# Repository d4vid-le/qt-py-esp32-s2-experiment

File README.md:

# qt-py-esp32-s2-experiment

A personal, non-production experiment: reconstruct the **Adafruit QT Py ESP32-S2
(Product 5325, Rev C)** in KiCad from the authoritative Eagle source, measuring
how accurately an AI agent can do it — and documenting every failure.

**This is not affiliated with or endorsed by Adafruit.** No boards are fabricated.

## Status

| Gate | Stage | Result |
|---|---|---|
| 0 | Inventory | ✅ 45 components, 34 nets, 159 pads; `.sch` vs `.brd` exact |
| 1 | Ground truth in KiCad | ✅ board imported; netlist identical after 2 ref renames; 57/57 pin audit |
| 2 | Schematic reconstruction | ✅ 45 components, 46 power symbols, 34/34 nets, 0 ERC errors |
| 3 | PCB | ✅ 45/45 placed, 17.78×20.701 outline, DRC run |
| 4 | Routing | ✅ 0 unconnected / 0 errors / 1.093 mm skew (verified reconstruction) |
| 5 | Manufacturing | ✅ Gerbers, drill, BOM, PnP, DFM, renders |

Read `reports/gate0-inventory.md`, `reports/gate1-ground-truth.md`,
`reports/gate1-u15-audit.md`, and `reports/gate2-schematic.md`.

## Attribution

The reference design is Adafruit's work, licensed **CC BY-SA 3.0 Unported**.
Verified in the source repository's
[`license.txt`](https://github.com/adafruit/Adafruit-QT-Py-ESP32-S2-PCB/blob/main/license.txt)
(shasum `075dad5e…86b74`):

- Product: https://www.adafruit.com/product/5325
- Learn guide: https://learn.adafruit.com/adafruit-qt-py-esp32-s2
- Downloads: https://learn.adafruit.com/adafruit-qt-py-esp32-s2/downloads
- Authoritative Eagle source: https://github.com/adafruit/Adafruit-QT-Py-ESP32-S2-PCB
- ESP32-S2 datasheet: https://cdn-learn.adafruit.com/assets/assets/000/096/705/original/esp32-s2_datasheet_en.pdf
- AP2112 datasheet: https://www.diodes.com/assets/Datasheets/AP2112.pdf

**Their Eagle files, PDFs and images are not committed here.** `reference/` is
gitignored; run `scripts/fetch-reference.sh` to pull them locally.

## Reproduce the netlist

```sh
scripts/fetch-reference.sh
python3 scripts/parse_eagle_netlist.py \
  "reference/eagle/Adafruit QT Py ESP32-S2 Rev C.sch" design
python3 scripts/compare_sch_brd.py \
  design/netlist_original.csv \
  "reference/eagle/Adafruit QT Py ESP32-S2 Rev C.brd"
python3 scripts/make_clean_bom.py \
  design/bom_original.csv design/bom_clean.csv design/bom_symbols.csv
```

Pin audit (needs PyMuPDF: `pip install -r scripts/requirements.txt`):

```sh
python3 scripts/parse_esp32s2_pins.py \
  reference/assets/esp32-s2_datasheet.pdf reference/imported-kicad/esp32s2-pins.csv
python3 scripts/make_u15_audit.py \
  "reference/eagle/Adafruit QT Py ESP32-S2 Rev C.sch" \
  reference/imported-kicad/esp32s2-pins.csv \
  design/netlist_original.csv design/u15-pinmap.csv
```

Import the board and diff it:

```sh
kicad-cli pcb import --format eagle \
  -o reference/imported-kicad/qt-py-esp32-s2.kicad_pcb \
  "reference/eagle/Adafruit QT Py ESP32-S2 Rev C.brd"

python3 scripts/extract_kicad_netlist.py \
  reference/imported-kicad/qt-py-esp32-s2.kicad_pcb \
  reference/imported-kicad/imported_netlist.csv

python3 scripts/diff_netlists.py \
  design/netlist_original.csv \
  reference/imported-kicad/imported_netlist.csv
```

## Layout

```
design/     ground-truth CSVs, STATE.md, checksums   (committed)
reports/    per-gate evidence                        (committed)
scripts/    parser, diff, fetch                      (committed)
renders/    PNG/JPG evidence                         (committed)
rebuild/    the KiCad reconstruction                 (Gate 2+)
reference/  Adafruit material + imported board       (gitignored)
```

## What is deliberately not here

- Adafruit's Eagle/PDF/image files (license + redistribution hygiene)
- `reference/`, venvs, `node_modules/`, secrets, logs
- Fabrication files: nothing is ordered or produced for manufacturing

## Notes

- KiCad 10.0.7, macOS arm64.
- The Eagle importer maps custom user layers 200/201 to `UNDEFINED`, which makes
  the imported board unloadable by DRC. Electrical data is unaffected. See the
  Gate 1 report.
- `kicad-sch-api` is not used: it does not embed `lib_symbols`.

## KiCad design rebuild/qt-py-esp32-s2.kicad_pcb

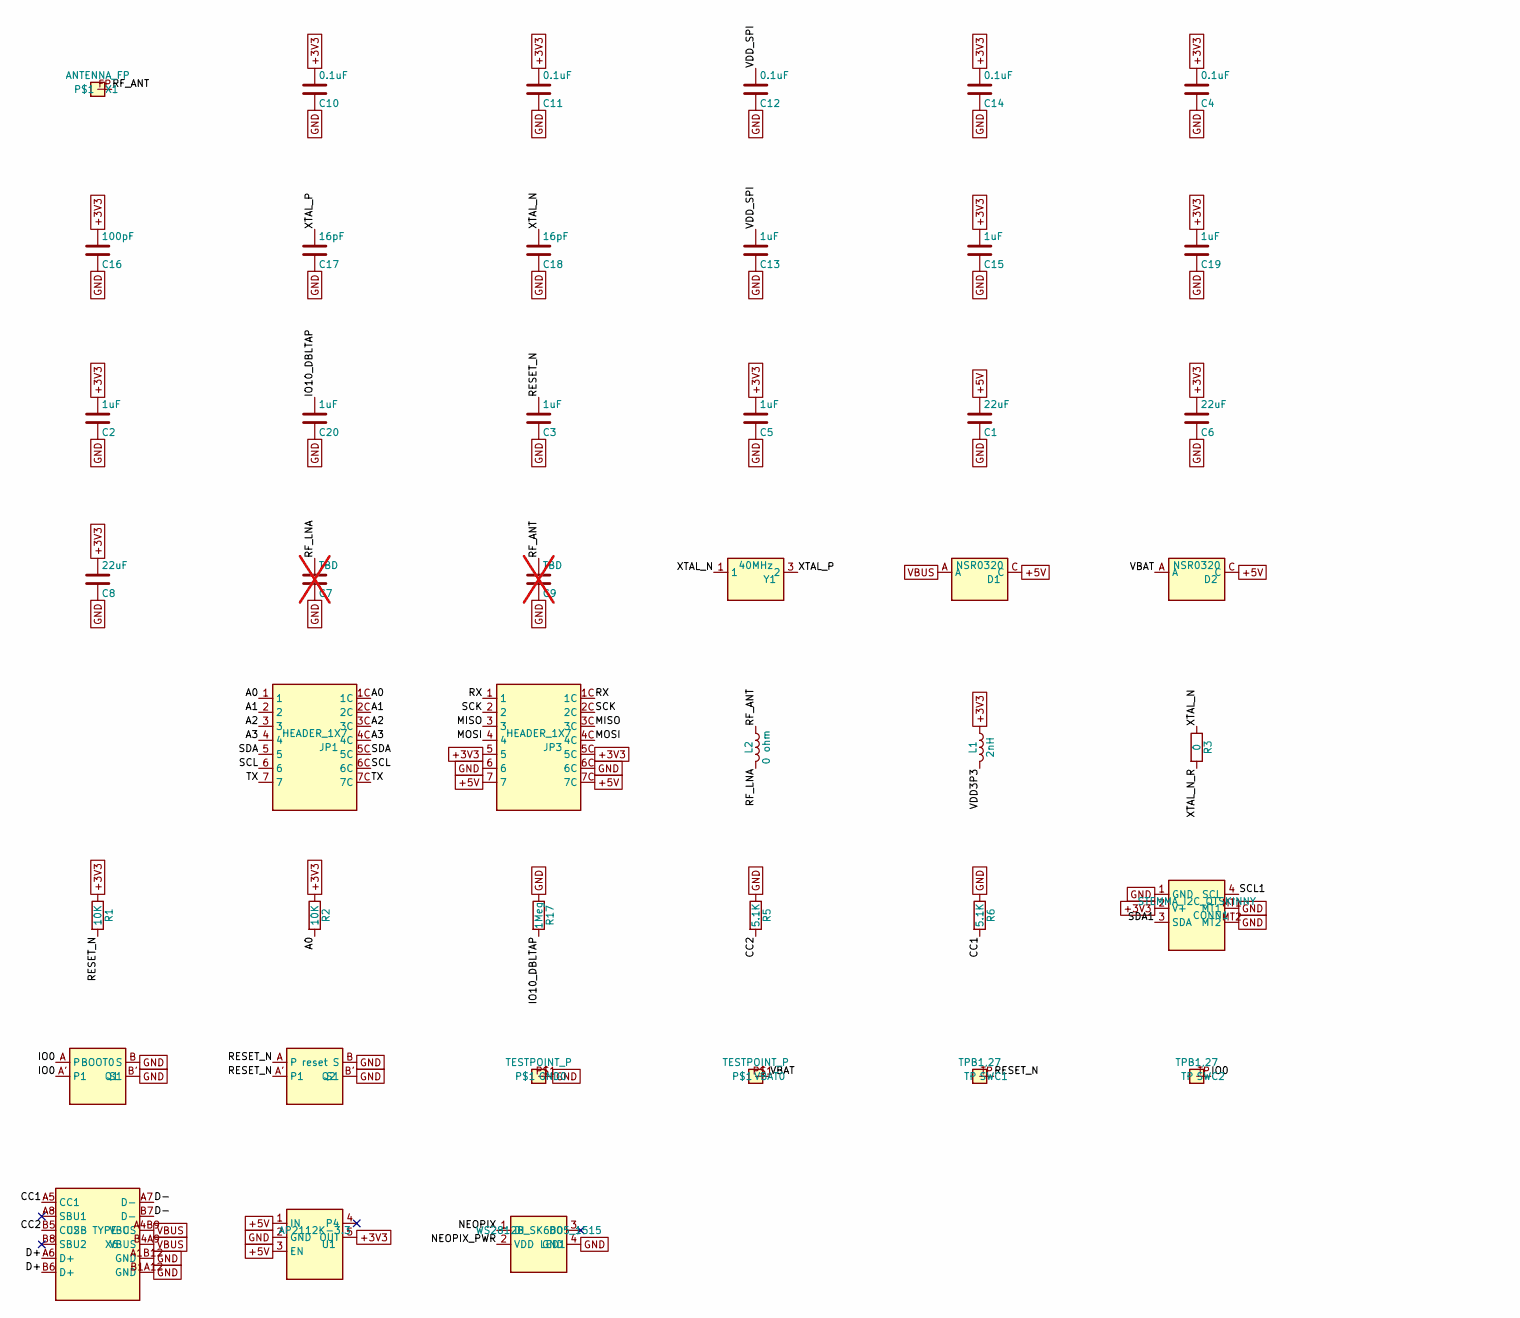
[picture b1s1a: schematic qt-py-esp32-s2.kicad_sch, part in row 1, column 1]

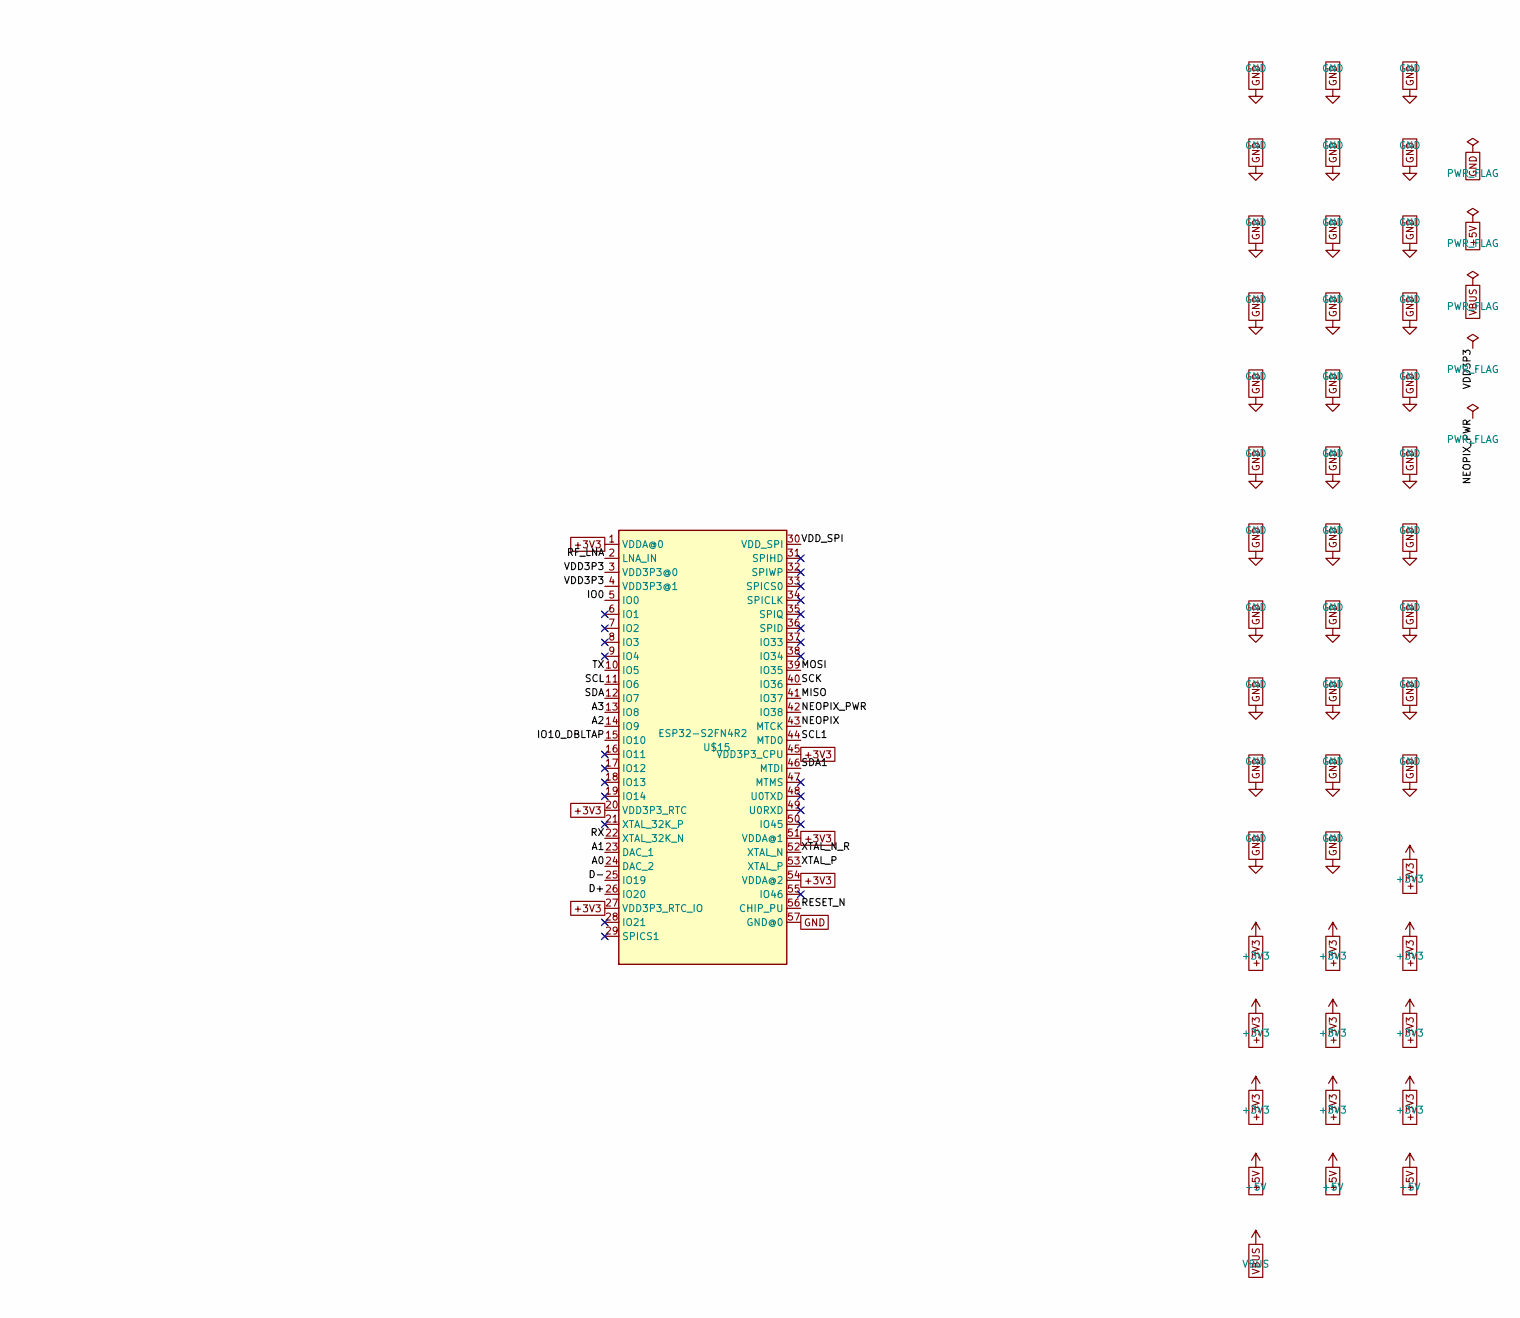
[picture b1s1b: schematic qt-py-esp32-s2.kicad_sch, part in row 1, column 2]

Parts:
C1, C6, C8: 22uF; C_0805_2012Metric
C2, C3, C5, C13, C15, C19, C20: 1uF; C_0402_1005Metric
C4, C10, C11, C12, C14: 0.1uF; C_0402_1005Metric
C7, C9: TBD; C_0402_1005Metric; not fitted
C16: 100pF; C_0402_1005Metric
C17, C18: 16pF; C_0402_1005Metric
CONN1: STEMMA_I2C_QTSKINNY; JST_SH4_SKINNY
D1, D2: NSR0320; SOD-323_MINI
GND0: TESTPOINT_P; TESTPOINT_MINUS_1X3MM
JP1, JP3: HEADER_1X7; 1X07_CASTEL
L1: 2nH; L_0402_1005Metric
L2: 0 ohm; L_0402_1005Metric
LED1: WS2812B_SK6805_1515; SK6805_1515
Q1: BOOT0; BTN_KMR2_4.6X2.8
Q2: reset; BTN_KMR2_4.6X2.8
R1, R2: 10K; R_0402_1005Metric
R3: 0; R_0402_1005Metric
R5, R6: 5.1K; R_0402_1005Metric
R17: 1Meg; R_0402_1005Metric
SWC1, SWC2: TPB1,27; B1_27
U1: AP2112K-3.3; SOT23-5
U$15: ESP32-S2FN4R2; QFN56_7X7
VBAT0: TESTPOINT_P; TESTPOINT_PLUS_1X3MM
X1: ANTENNA_FP; ANT_2450AT18B100
X6: USB TYPE C; USB_C_CUSB31-CFM2AX-01-X
Y1: 40MHz; CRYSTAL_2X1.6

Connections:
+3V3: C2.1, C4.1, C5.1, C6.1, C8.1, C10.1, C11.1, C14.1, C15.1, C16.1, C19.1, CONN1.2 (V+), JP3.5, JP3.5C, L1.1, R1.1, R2.1, U1.5 (OUT), U$15.1 (VDDA@0), U$15.20 (VDD3P3_RTC), U$15.27 (VDD3P3_RTC_IO), U$15.45 (VDD3P3_CPU), U$15.51 (VDDA@1), U$15.54 (VDDA@2)
+5V: C1.1, D1.C, D2.C, JP3.7, JP3.7C, U1.1 (IN), U1.3 (EN)
A0: JP1.1, JP1.1C, R2.2, U$15.24 (DAC_2)
A1: JP1.2, JP1.2C, U$15.23 (DAC_1)
A2: JP1.3, JP1.3C, U$15.14 (IO9)
A3: JP1.4, JP1.4C, U$15.13 (IO8)
CC1: R6.2, X6.A5 (CC1)
CC2: R5.2, X6.B5 (CC2)
D+: U$15.26 (IO20), X6.A6 (D+), X6.B6 (D+)
D-: U$15.25 (IO19), X6.A7 (D-), X6.B7 (D-)
GND: C1.2, C2.2, C3.2, C4.2, C5.2, C6.2, C7.2, C8.2, C9.2, C10.2, C11.2, C12.2, C13.2, C14.2, C15.2, C16.2, C17.2, C18.2, C19.2, C20.2, CONN1.1 (GND), CONN1.MT1, CONN1.MT2, GND0.P$1, JP3.6, JP3.6C, LED1.4 (GND), Q1.B (S), Q1.B' (S1), Q2.B (S), Q2.B' (S1), R5.1, R6.1, R17.1, U1.2 (GND), U$15.57 (GND@0), X6.A1B12 (GND), X6.B1A12 (GND)
IO0: Q1.A, Q1.A' (P1), SWC2.TP, U$15.5 (IO0)
IO10_DBLTAP: C20.1, R17.2, U$15.15 (IO10)
MISO: JP3.3, JP3.3C, U$15.41 (IO37)
MOSI: JP3.4, JP3.4C, U$15.39 (IO35)
NEOPIX: LED1.1 (DI), U$15.43 (MTCK)
NEOPIX_PWR: LED1.2 (VDD), U$15.42 (IO38)
RESET_N: C3.1, Q2.A, Q2.A' (P1), R1.2, SWC1.TP, U$15.56 (CHIP_PU)
RF_ANT: C9.1, L2.1, X1.FP
RF_LNA: C7.1, L2.2, U$15.2 (LNA_IN)
RX: JP3.1, JP3.1C, U$15.22 (XTAL_32K_N)
SCK: JP3.2, JP3.2C, U$15.40 (IO36)
SCL: JP1.6, JP1.6C, U$15.11 (IO6)
SCL1: CONN1.4 (SCL), U$15.44 (MTD0)
SDA: JP1.5, JP1.5C, U$15.12 (IO7)
SDA1: CONN1.3 (SDA), U$15.46 (MTDI)
TX: JP1.7, JP1.7C, U$15.10 (IO5)
VBAT: D2.A, VBAT0.P$1
VBUS: D1.A, X6.A4B9 (VBUS), X6.B4A9 (VBUS)
VDD3P3: L1.2, U$15.3 (VDD3P3@0), U$15.4 (VDD3P3@1)
VDD_SPI: C12.1, C13.1, U$15.30 (VDD_SPI)
XTAL_N: C18.1, R3.1, Y1.1
XTAL_N_R: R3.2, U$15.52 (XTAL_N)
XTAL_P: C17.1, U$15.53 (XTAL_P), Y1.3 (2)

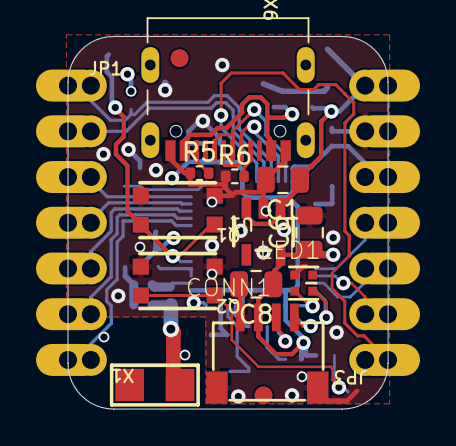
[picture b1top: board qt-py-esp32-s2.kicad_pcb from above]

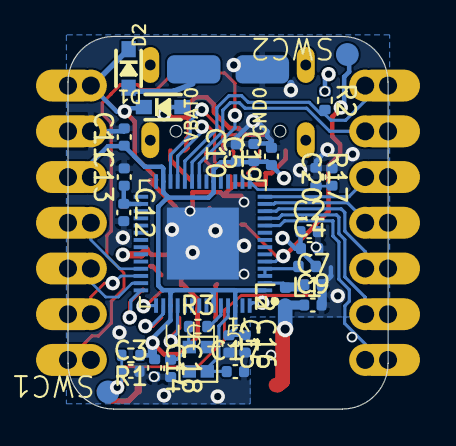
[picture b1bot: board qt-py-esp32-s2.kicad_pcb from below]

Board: 4 copper layers, 17.8 x 20.7 mm, 47 parts (31 on the bottom side), 34 nets.

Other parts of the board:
FID1, FID2: FIDUCIAL_1MM

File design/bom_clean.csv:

item,qty,refs,value,device,package,library,populate,dnp,note
1,1,X1,,ANTENNA_JOHANSON_2450AT18B100,ANT_2450AT18B100,adafruit_wireless,yes,no,
2,5,C10 C11 C12 C14 C4,0.1uF,CAP_CERAMIC,_0402NO,microbuilder,yes,no,
3,1,C16,100pF,CAP_CERAMIC,_0402NO,microbuilder,yes,no,
4,2,C17 C18,16pF,CAP_CERAMIC,_0402NO,microbuilder,yes,no,
5,7,C13 C15 C19 C2 C20 C3 C5,1uF,CAP_CERAMIC,_0402NO,microbuilder,yes,no,
6,3,C1 C6 C8,22uF,CAP_CERAMIC,0805-NO,microbuilder,yes,no,
7,2,C7 C9,TBD,CAP_CERAMIC,_0402NO,microbuilder,no,yes,TBD in source; DNP; antenna match placeholder
8,1,Y1,40MHz,CRYSTAL,CRYSTAL_2X1.6,microbuilder,yes,no,
9,2,D1 D2,NSR0320,DIODE,SOD-323_MINI,microbuilder,yes,no,
10,1,U$15,,ESP32-S2,QFN56_7X7,adafruit_wireless,yes,no,
11,2,JP1 JP3,,HEADER-1X7,1X07_CASTEL,microbuilder,yes,no,
12,1,L2,0 ohm,INDUCTOR,_0402,microbuilder,yes,no,
13,1,L1,2nH,INDUCTOR,_0402,microbuilder,yes,no,
14,1,R3,0,RESISTOR,_0402NO,microbuilder,yes,no,"0R in series with crystal XTAL_N; source quirk, preserved"
15,2,R1 R2,10K,RESISTOR,_0402NO,microbuilder,yes,no,
16,1,R17,1Meg,RESISTOR,_0402NO,microbuilder,yes,no,
17,2,R5 R6,5.1K,RESISTOR,_0402NO,microbuilder,yes,no,
18,1,CONN1,STEMMA_I2C_QTSKINNY,STEMMA_I2C,JST_SH4_SKINNY,microbuilder,yes,no,
19,1,Q1,BOOT0,SWITCH_TACT_SMT,BTN_KMR2_4.6X2.8,adafruit_electromech,yes,no,
20,1,Q2,reset,SWITCH_TACT_SMT,BTN_KMR2_4.6X2.8,adafruit_electromech,yes,no,
21,1,GND,,TESTPOINT,TESTPOINT_MINUS_1X3MM,microbuilder,yes,no,
22,1,VBAT,,TESTPOINT,TESTPOINT_PLUS_1X3MM,microbuilder,yes,no,
23,2,SWC1 SWC2,"TPB1,27",TP,"B1,27",testpad,yes,no,
24,1,X6,USB TYPE C,USB_C,USB_C_CUSB31-CFM2AX-01-X,adafruit_electromech,yes,no,
25,1,U1,AP2112K-3.3,VREG_SOT23-5,SOT23-5,adafruit_power,yes,no,
26,1,LED1,WS2812B_SK6805_1515,WS2812B,SK6805_1515,microbuilder,yes,no,
